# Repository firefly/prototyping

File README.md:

Prototyping
===========

This repository hosts various experimental designs, tools,
development boards, etc. that we are trying out or using
to develop Firefly.

Development Boards
------------------

- [Jekyll One](./mixing-board-jekyll/)

License
-------

MIT License.

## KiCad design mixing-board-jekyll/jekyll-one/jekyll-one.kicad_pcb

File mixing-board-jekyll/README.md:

Mixing Board: Jekyll One
========================

The mixing board is a hodge podge of components, with very
little thought put into layout, routing and labels and
includes myriad headers to organize their connection.

It is meant to make it easy to re-wire and experiment with
various routing options and includes a variety of components
for evaluation.

It is also an opportunity to try out a real-world PCB with
footprint layouts.

Components
----------

See [thirdparty-datasheets](https://github.com/firefly/thirdparty-datasheets/#displays) for more details.

- ZJY133T-IF05 display
- USB-C with a AMS1117-3.3 as a power sub-system
- ESP32-C3-MINI-1 MCU module
- 4x tactile buttons

Pins
----

- MCU
  - Full ESP32-C3-MINI-1 GPIO pins, 3V3 and enable
- USB Power Sub-system
  - 3.3v power rail
  - ground rail
  - exposed CC1, CC2 and shield
- Display
  - Full 24-pin connector for FPC with both normal and inverted connection
- 4x Buttons

Design
------

Current Focus
-------------

- wiring arrangement and routing for the display
- wiring arrangement and routing for the buttons
- effectiveness of the AMS1117-3.3 via USB-C
- footprint for the USB-C connector
- footprint for the screen as a top-mounted

Notes
-----

- obviously this should not be used for any production purposes

License
-------

MIT License.

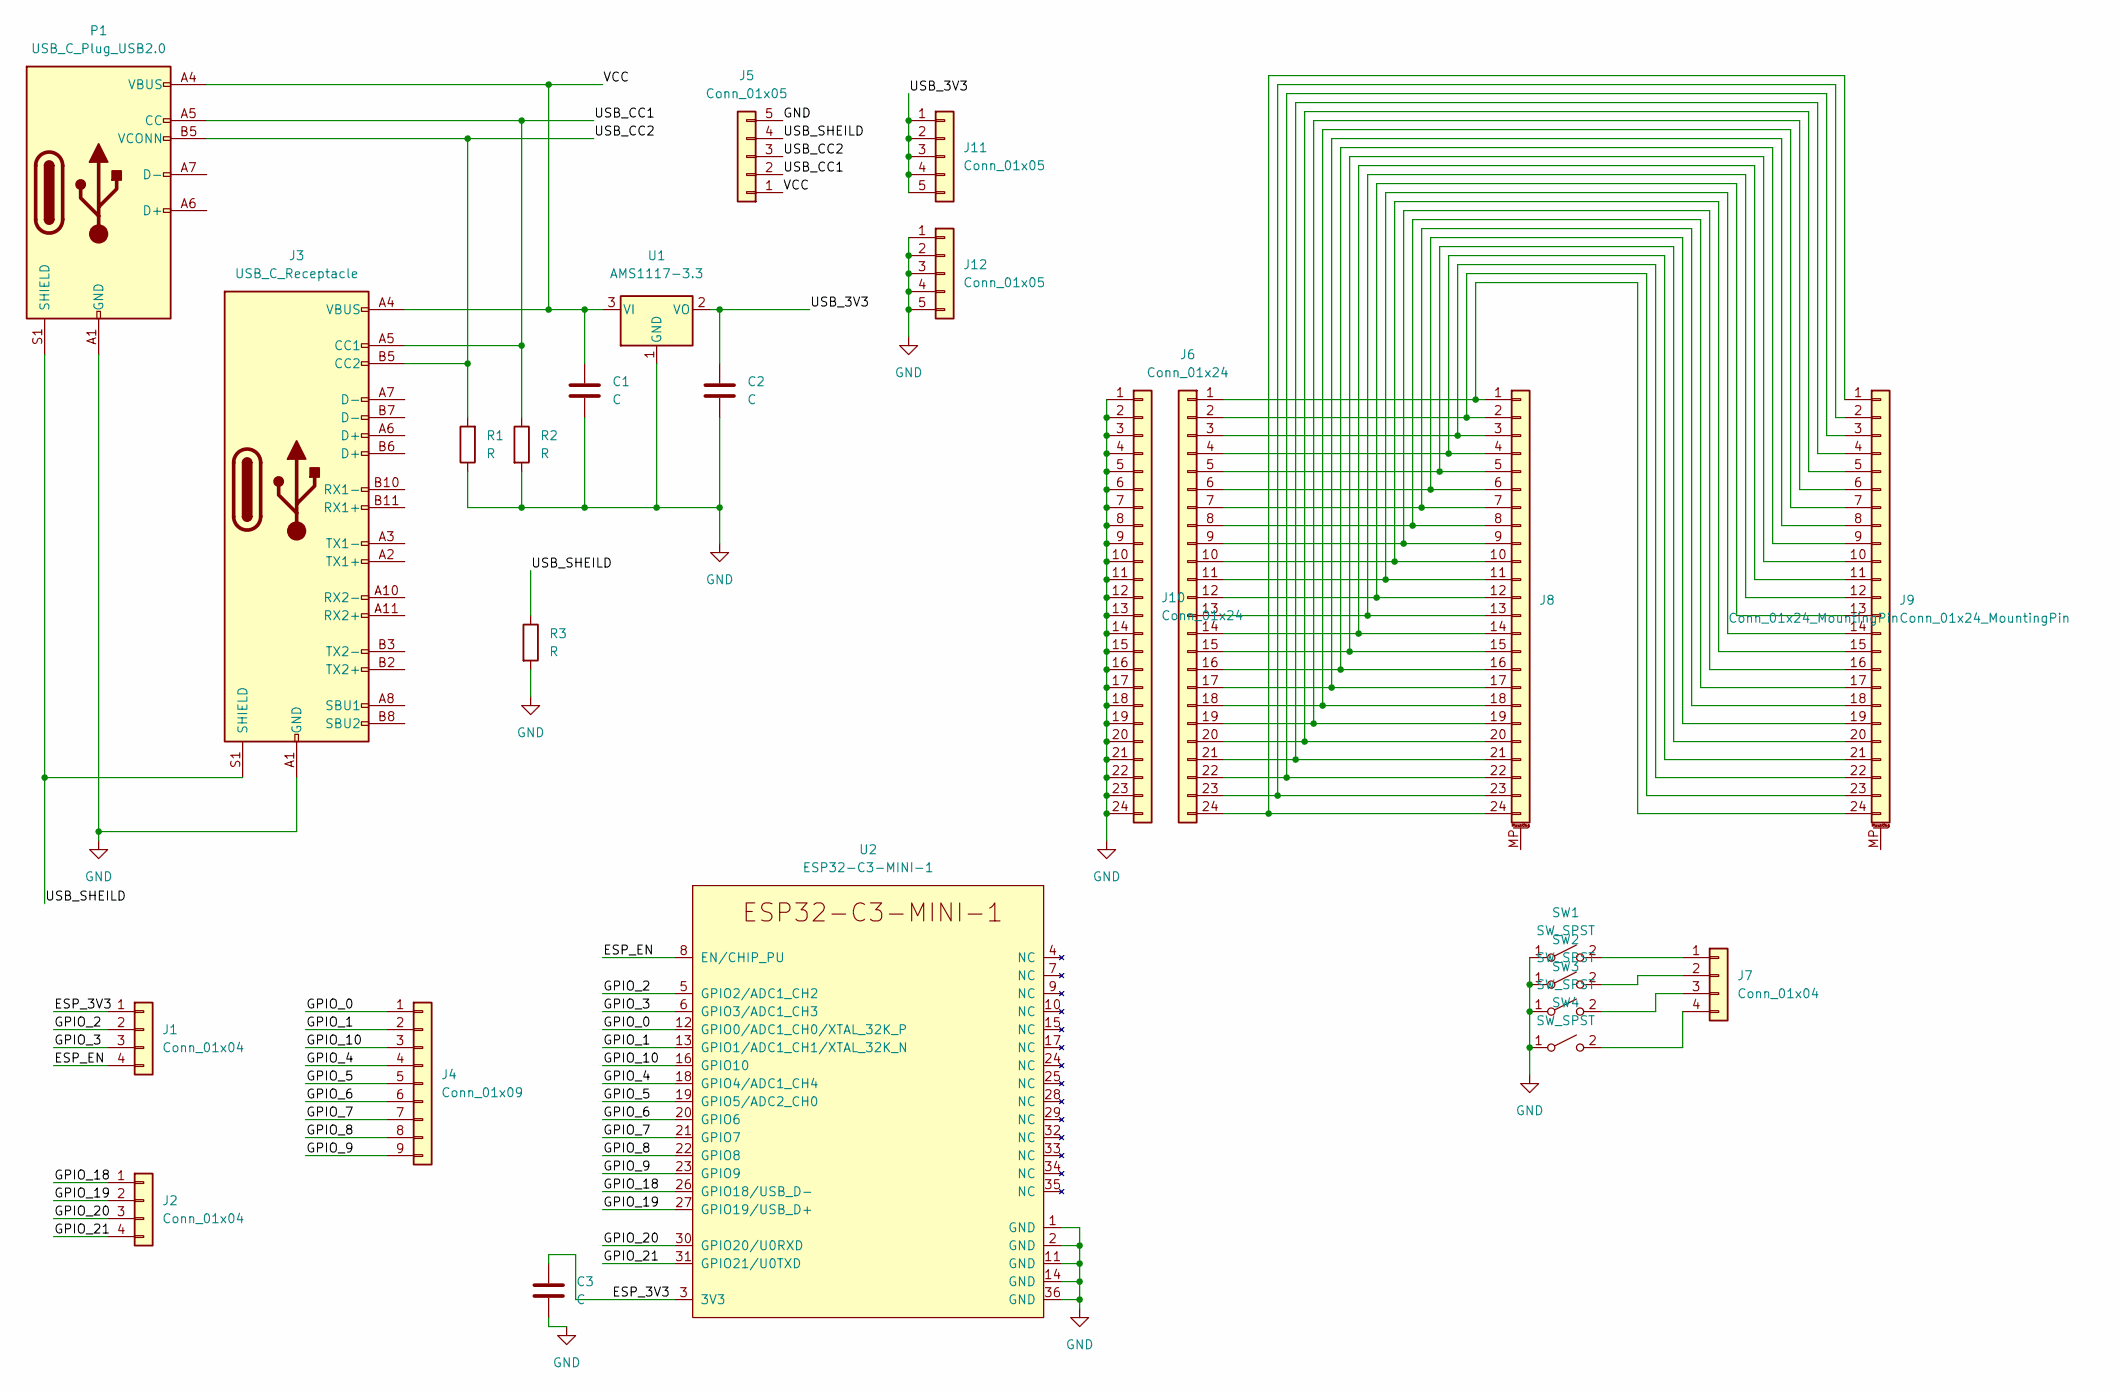
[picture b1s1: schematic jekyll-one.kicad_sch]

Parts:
C1, C3: C; C_0805_2012Metric_Pad1.18x1.45mm_HandSolder
C2: C; C_1206_3216Metric_Pad1.33x1.80mm_HandSolder
J1, J2, J7: Conn_01x04; PinHeader_1x04_P2.54mm_Vertical
J3: USB_C_Receptacle; USB_C_Receptacle_XKB_U262-16XN-4BVC11
J4: Conn_01x09; PinHeader_1x09_P2.54mm_Vertical
J5, J11, J12: Conn_01x05; PinHeader_1x05_P2.54mm_Vertical
J6, J10: Conn_01x24; PinHeader_1x24_P2.54mm_Vertical
J8, J9: Conn_01x24_MountingPin; Hirose_FH12-24S-0.5SH_1x24-1MP_P0.50mm_Horizontal
P1: USB_C_Plug_USB2.0
R1, R2, R3: R; R_0805_2012Metric_Pad1.20x1.40mm_HandSolder
SW1, SW2, SW3, SW4: SW_SPST; SW_SPST_SKQG_WithStem
U1: AMS1117-3.3; SOT-223-3_TabPin2
U2: ESP32-C3-MINI-1

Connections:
/ESP_3V3: C3.1, J1.1, U2.3 (3V3)
/ESP_EN: J1.4, U2.8 (EN/CHIP_PU)
/GPIO_0: J4.1, U2.12 (GPIO0/ADC1_CH0/XTAL_32K_P)
/GPIO_1: J4.2, U2.13 (GPIO1/ADC1_CH1/XTAL_32K_N)
/GPIO_2: J1.2, U2.5 (GPIO2/ADC1_CH2)
/GPIO_3: J1.3, U2.6 (GPIO3/ADC1_CH3)
/GPIO_4: J4.4, U2.18 (GPIO4/ADC1_CH4)
/GPIO_5: J4.5, U2.19 (GPIO5/ADC2_CH0)
/GPIO_6: J4.6, U2.20 (GPIO6)
/GPIO_7: J4.7, U2.21 (GPIO7)
/GPIO_8: J4.8, U2.22 (GPIO8)
/GPIO_9: J4.9, U2.23 (GPIO9)
/GPIO_10: J4.3, U2.16 (GPIO10)
/GPIO_18: J2.1, U2.26 (GPIO18/USB_D-)
/GPIO_19: J2.2, U2.27 (GPIO19/USB_D+)
/GPIO_20: J2.3, U2.30 (GPIO20/U0RXD)
/GPIO_21: J2.4, U2.31 (GPIO21/U0TXD)
/USB_3V3: C2.1, J11.1, J11.2, J11.3, J11.4, J11.5, U1.2 (VO)
/USB_CC1: J3.A5 (CC1), J5.2, P1.A5 (CC), R2.1
/USB_CC2: J3.B5 (CC2), J5.3, P1.B5 (VCONN), R1.2
/USB_SHEILD: J3.S1 (SHIELD), J5.4, P1.S1 (SHIELD), R3.1
/VCC: C1.1, J3.A4 (VBUS), J3.A9 (VBUS), J3.B4 (VBUS), J3.B9 (VBUS), J5.1, P1.A4 (VBUS), P1.A9 (VBUS), P1.B4 (VBUS), P1.B9 (VBUS), U1.3 (VI)
GND: C1.2, C2.2, C3.2, J3.A1 (GND), J3.A12 (GND), J3.B1 (GND), J3.B12 (GND), J5.5, J10.1, J10.2, J10.3, J10.4, J10.5, J10.6, J10.7, J10.8, J10.9, J10.10, J10.11, J10.12, J10.13, J10.14, J10.15, J10.16, J10.17, J10.18, J10.19, J10.20, J10.21, J10.22, J10.23, J10.24, J12.1, J12.2, J12.3, J12.4, J12.5, P1.A1 (GND), P1.A12 (GND), P1.B1 (GND), P1.B12 (GND), R1.1, R2.2, R3.2, SW1.1 (A), SW2.1 (A), SW3.1 (A), SW4.1 (A), U1.1 (GND), U2.1 (GND), U2.2 (GND), U2.11 (GND), U2.14 (GND), U2.36 (GND)
unnamed: J6.1, J8.1, J9.24
unnamed: J6.2, J8.2, J9.23
unnamed: J6.3, J8.3, J9.22
unnamed: J6.4, J8.4, J9.21
unnamed: J6.5, J8.5, J9.20
unnamed: J6.6, J8.6, J9.19
unnamed: J6.7, J8.7, J9.18
unnamed: J6.8, J8.8, J9.17
unnamed: J6.9, J8.9, J9.16
unnamed: J6.10, J8.10, J9.15
unnamed: J6.11, J8.11, J9.14
unnamed: J6.12, J8.12, J9.13
unnamed: J6.13, J8.13, J9.12
unnamed: J6.14, J8.14, J9.11
unnamed: J6.15, J8.15, J9.10
unnamed: J6.16, J8.16, J9.9
unnamed: J6.17, J8.17, J9.8
unnamed: J6.18, J8.18, J9.7
unnamed: J6.19, J8.19, J9.6
unnamed: J6.20, J8.20, J9.5
unnamed: J6.21, J8.21, J9.4
unnamed: J6.22, J8.22, J9.3
unnamed: J6.23, J8.23, J9.2
unnamed: J6.24, J8.24, J9.1
unnamed: J7.1, SW1.2 (B)
unnamed: J7.2, SW2.2 (B)
unnamed: J7.3, SW3.2 (B)
unnamed: J7.4, SW4.2 (B)

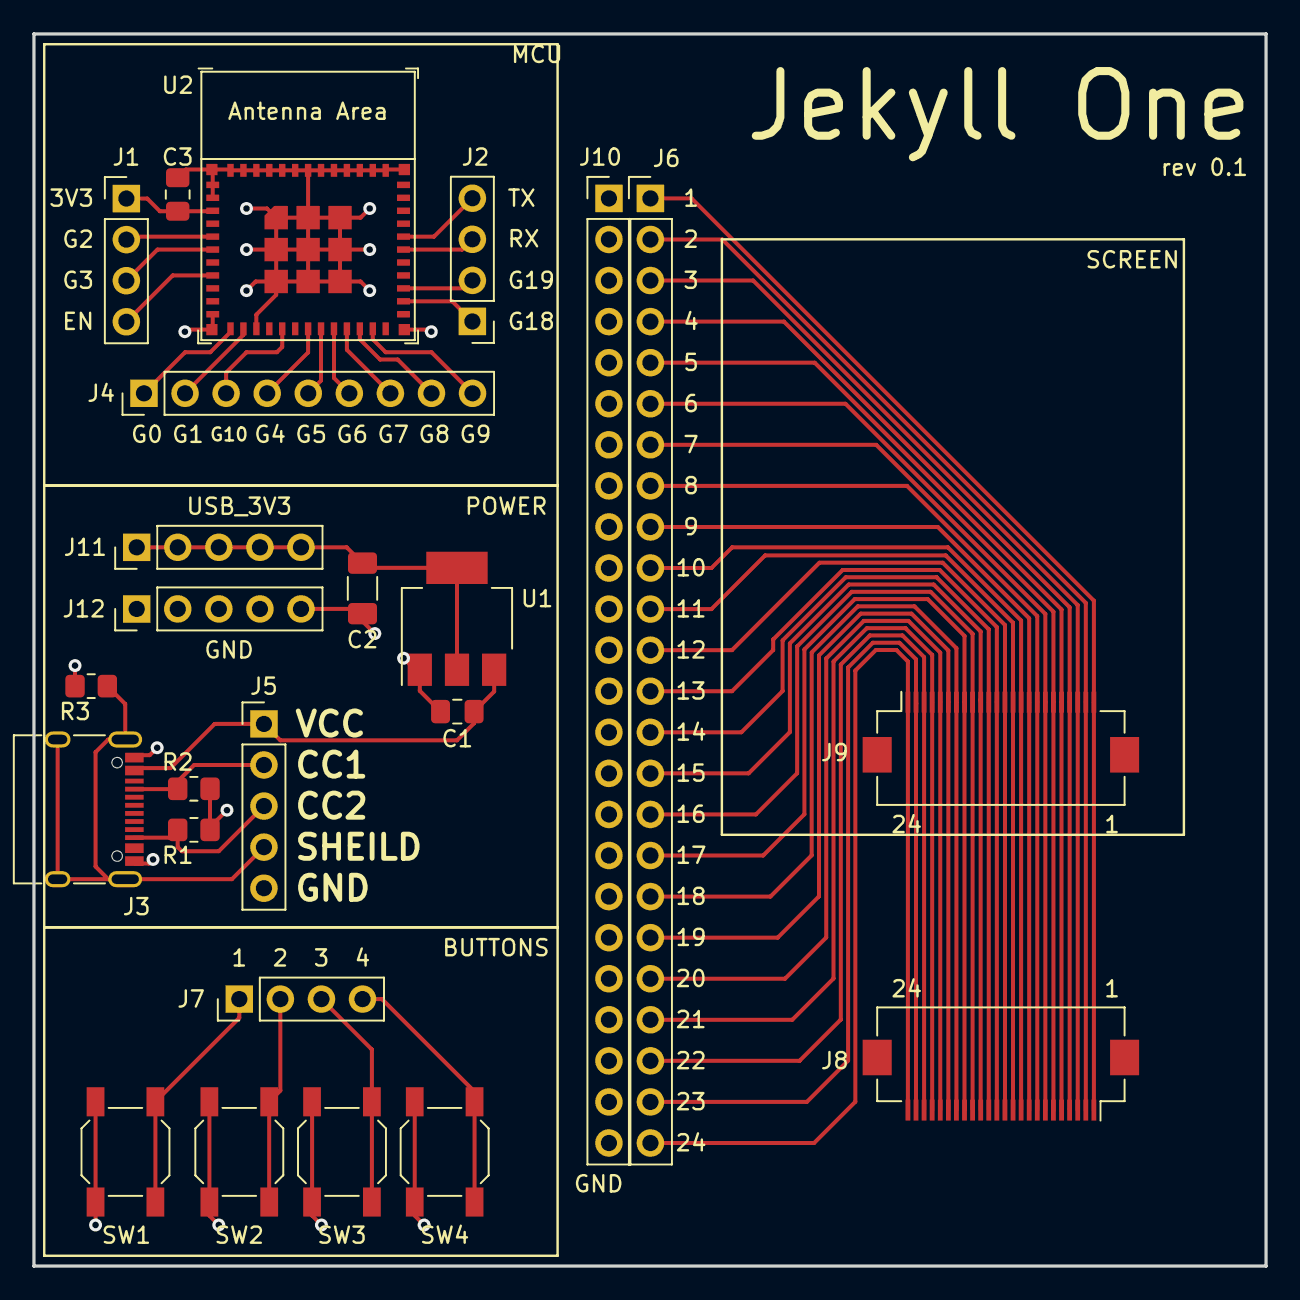
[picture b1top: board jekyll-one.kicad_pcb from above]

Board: 2 copper layers, 76.2 x 76.2 mm, 24 parts (0 on the bottom side), 51 nets.

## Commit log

2022-09-14 Initial code drop.
2022-09-15 Added initial Jekyll One design.
2022-09-15 Added Espressif KiCad libraries.
2022-09-15 Use local thirdparty libraries.
2022-09-15 admin: add gitignore
2022-09-15 docs: fix typo
2022-09-15 Added some images of the design.
